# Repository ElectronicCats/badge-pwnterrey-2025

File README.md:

# Badge PWNterrey 2025
Los patitos llegaron es el badge electronico de [PWNTERREY]([https://hackgdl.net/](https://pwnterrey.net/))

## Características

- Microcontrolador Puya PY32F002AA15M6TU
- Baterias CR2030
- 4 LEDs SMD

# Firmware
- Para hacer cambios en el firmware revisar nuestros [PUYA Projects](https://github.com/ElectronicCats/puya-projects)

## License

Diseñado por Electronic Cats para HackGDL

Electronic Cats invests time and resources in providing this open-source design. Please support Electronic Cats and open-source hardware by purchasing products from Electronic Cats!

Hardware released under

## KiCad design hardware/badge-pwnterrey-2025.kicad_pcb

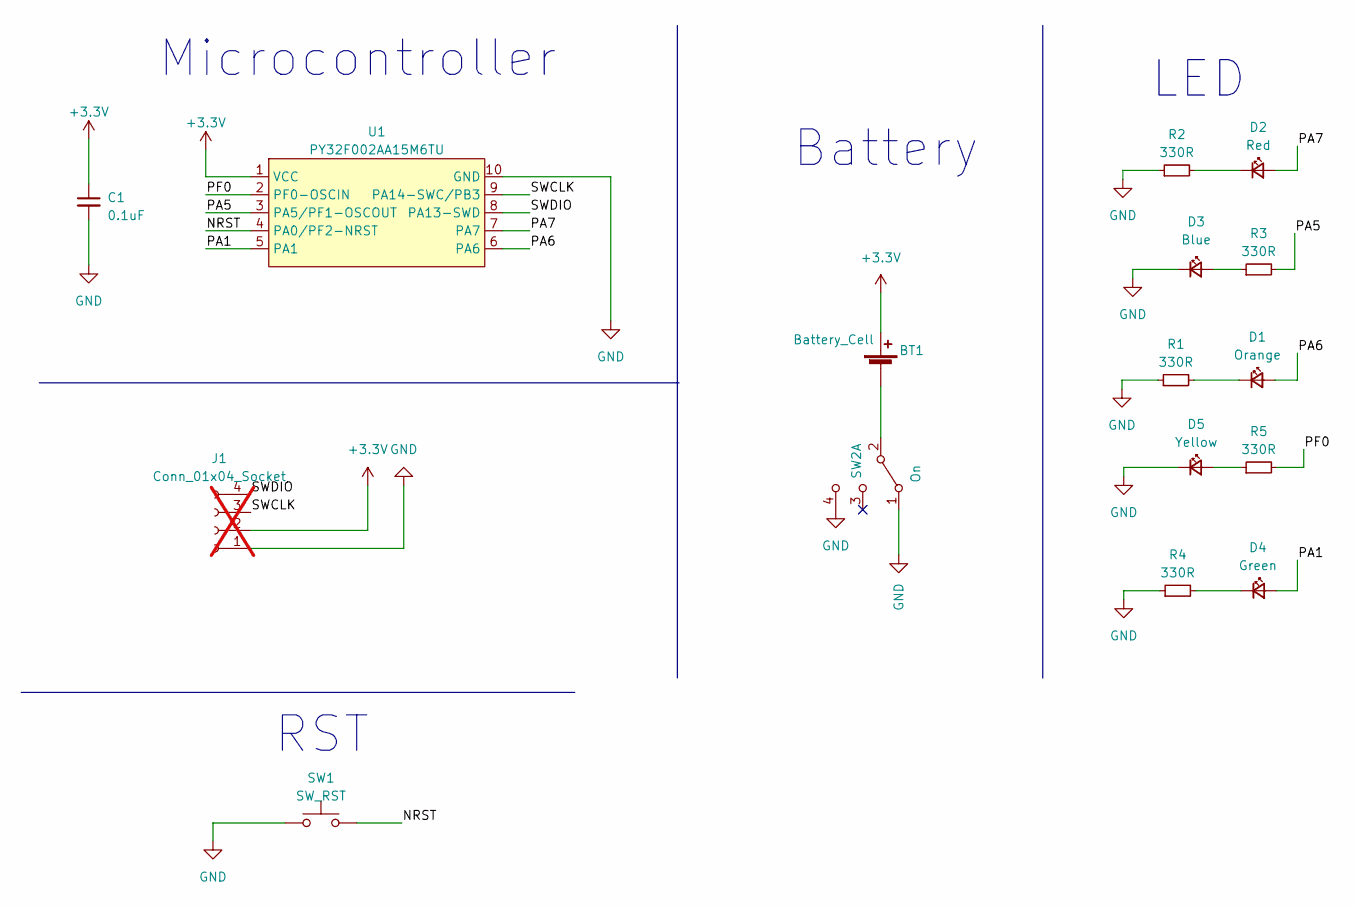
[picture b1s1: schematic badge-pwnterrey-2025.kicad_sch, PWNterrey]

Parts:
BT1: Battery_Cell; BAT-HLD-001; LCSC# C964833
C1: 0.1uF; C_0805_2012Metric; LCSC# C235731
D1: Orange; LED_0805_2012Metric; LCSC# C434437
D2: Red; LED_0805_2012Metric; LCSC# C965812
D3: Blue; LED_0805_2012Metric; LCSC# C205441
D4: Green; LED_0805_2012Metric; LCSC# C965815
D5: Yellow; LED_0805_2012Metric; LCSC# C84261
J1: Conn_01x04_Socket; PinHeader_1x04_P2.54mm_Vertical; not fitted
R1, R2, R3, R4, R5: 330R; R_0805_2012Metric; LCSC# C119075
SW1: SW_RST; SW_SPST_TL3342; LCSC# C318889
SW2: On; MSK12C02; LCSC# C431540
U1: PY32F002AA15M6TU; PY32F002AA15M; LCSC# C5292058

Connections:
+3.3V: BT1.2 (+), C1.1, J1.2, U1.1 (VCC)
/NRST: SW1.2, U1.4 (PA0/PF2-NRST)
/PA1: D4.2 (A), U1.5 (PA1)
/PA5: R3.2, U1.3 (PA5/PF1-OSCOUT)
/PA6: D1.2 (A), U1.6 (PA6)
/PA7: D2.2 (A), U1.7 (PA7)
/PF0: R5.2, U1.2 (PF0-OSCIN)
/SWCLK: J1.3, U1.9 (PA14-SWC/PB3)
/SWDIO: J1.4, U1.8 (PA13-SWD)
GND: C1.2, D3.1 (K), D5.1 (K), J1.1, R1.1, R2.1, R4.1, SW1.1, SW2.1 (A), SW2.4 (C), U1.10 (GND)
unnamed: BT1.1 (-), SW2.2 (B)
unnamed: D1.1 (K), R1.2
unnamed: D2.1 (K), R2.2
unnamed: D3.2 (A), R3.1
unnamed: D4.1 (K), R4.2
unnamed: D5.2 (A), R5.1

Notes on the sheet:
LED
Battery
Microcontroller
RST

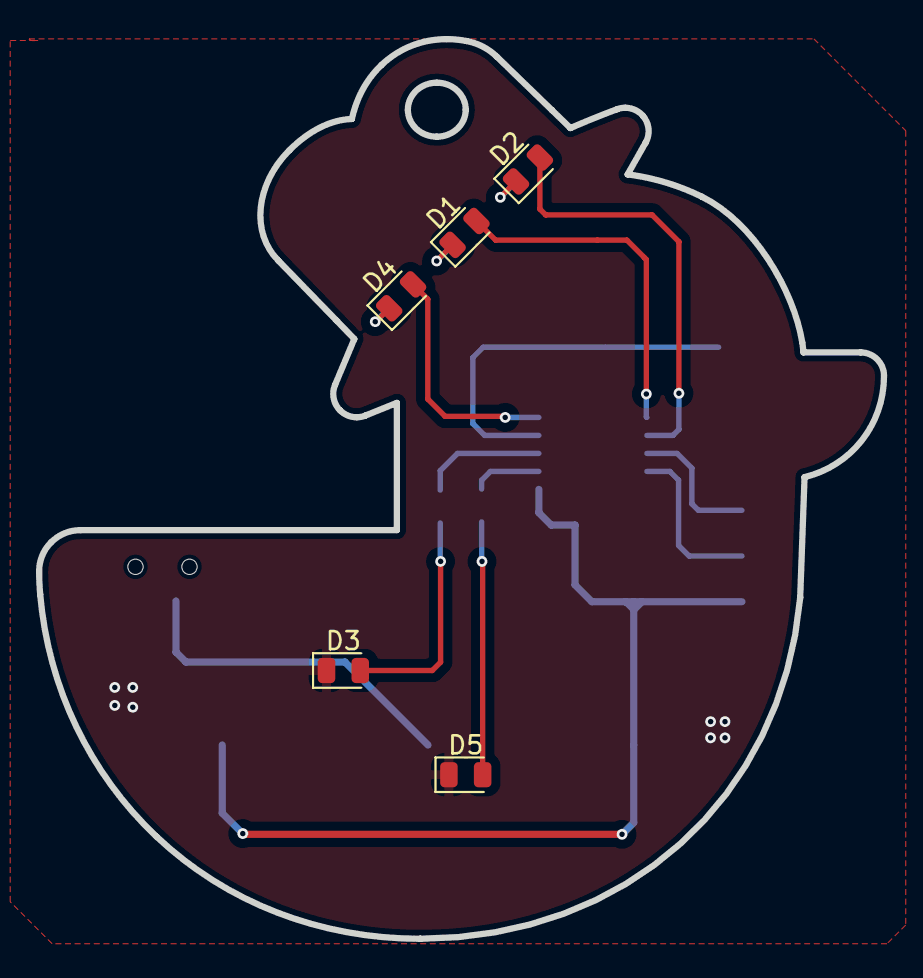
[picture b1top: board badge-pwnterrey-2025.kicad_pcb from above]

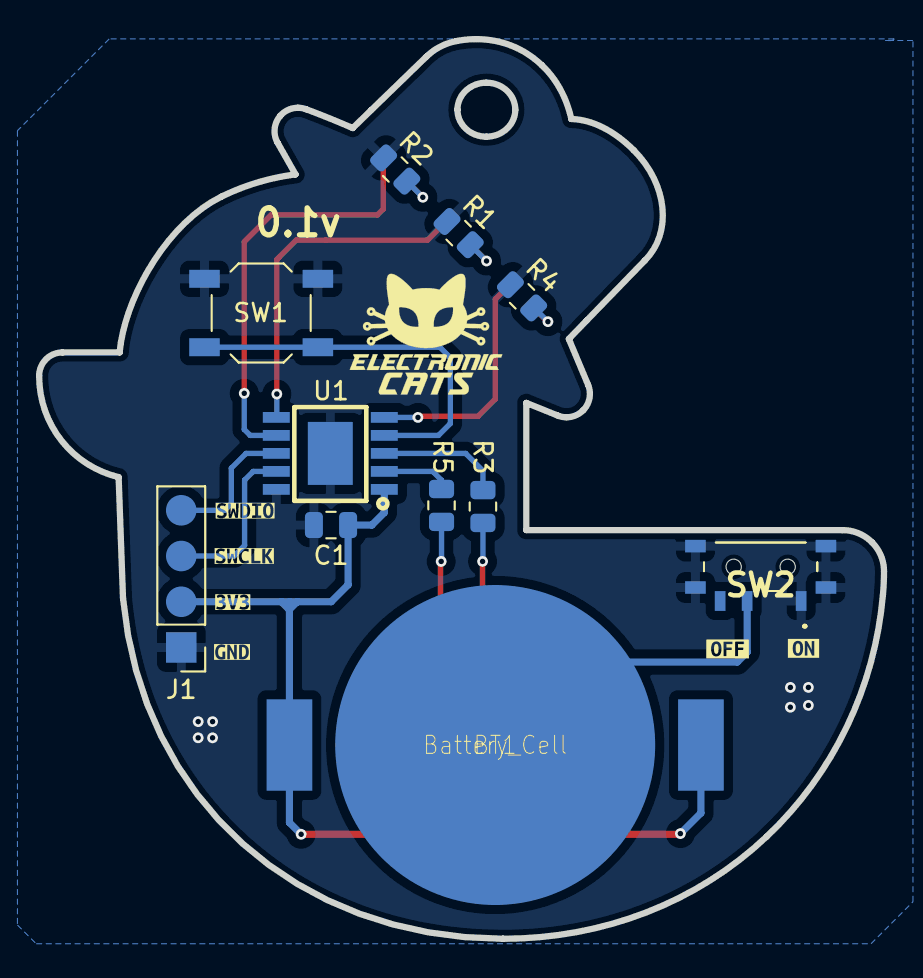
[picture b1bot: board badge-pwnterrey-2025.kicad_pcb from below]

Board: 2 copper layers, 46.9 x 50.0 mm, 22 parts (17 on the bottom side), 16 nets.

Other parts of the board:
kibuzzard-67D45E5B: G***; kibuzzard-67D45E5B
kibuzzard-67D45E75: G***; kibuzzard-67D45E75
kibuzzard-67D45F14: G***; kibuzzard-67D45F14
kibuzzard-67D45F29: G***; kibuzzard-67D45F29
kibuzzard-67D45F47: G***; kibuzzard-67D45F47
kibuzzard-67D45F59: G***; kibuzzard-67D45F59

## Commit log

2025-03-11 feat(hw): create kicad project
2025-03-11 feat(hw): add board outline
2025-03-11 feat(hw): add schematic
2025-03-12 feat(hw): add floorplan
2025-03-13 feat(hw): add routes
2025-03-14 feat(Hw):Added_Labels
2025-03-14 feat(hw): move routes
2025-04-28 feat(fw): initial commit
2025-04-28 feat(Fw):Update_firmware
2025-05-27 docs: Update README.md
